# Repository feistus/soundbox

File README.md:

# Soundbox
This device plays soundfiles from a SD Card using the [https://github.com/TMRh20/TMRpcm](TMRpcm) lib.

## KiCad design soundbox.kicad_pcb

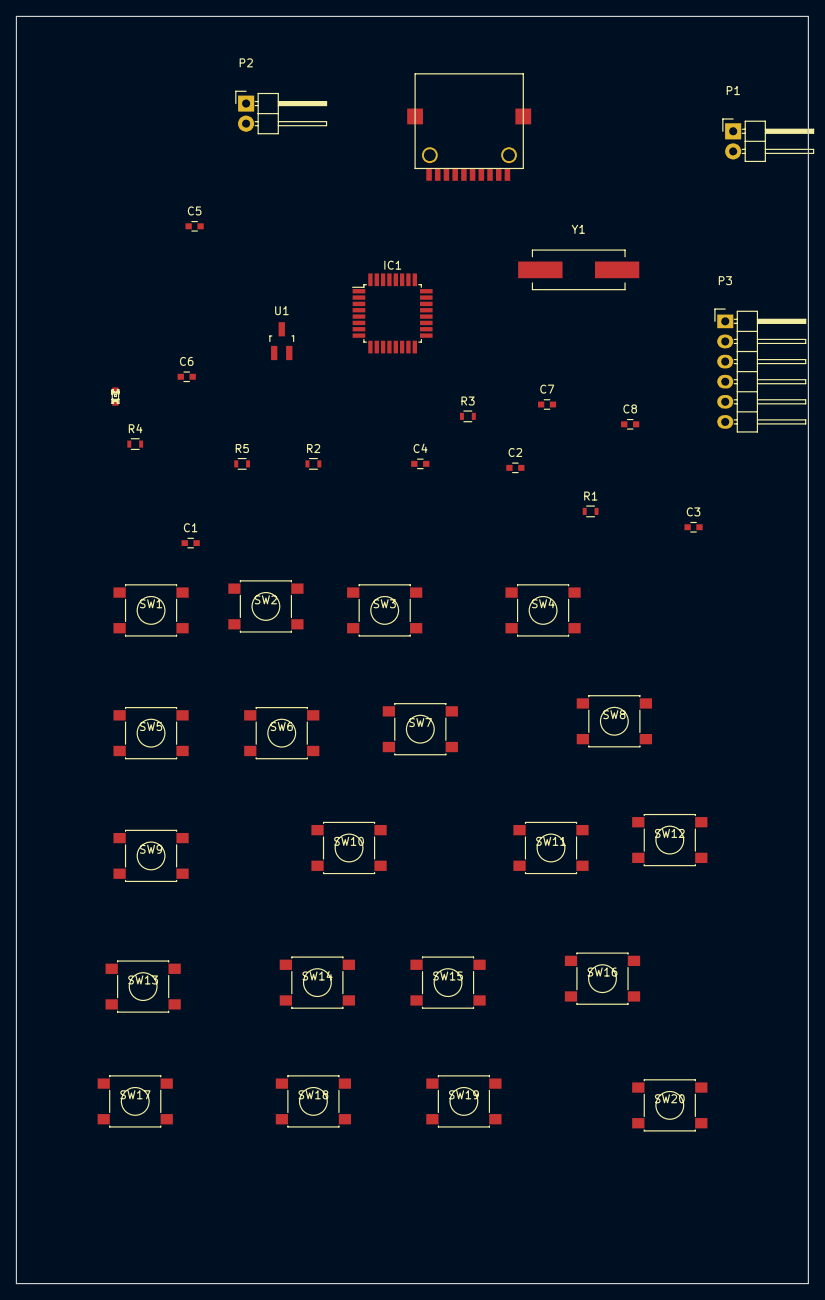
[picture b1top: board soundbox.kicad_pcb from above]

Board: 2 copper layers, 100.0 x 160.0 mm, 41 parts (0 on the bottom side), 27 nets, no tracks yet.

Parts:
C1, C2, C3, C4, C5, C8: 100n; C_0603
C6, C7: 23p; C_0603
D1: LED; led-CHIPLED_0603
IC1: ATMEGA328-A; TQFP-32_7x7mm_Pitch0.8mm
J1: µSD; MICRO_SD_CARD_HOLDER
P1, P2: CONN_01X02; Pin_Header_Angled_1x02
P3: CONN_01X06; Pin_Header_Angled_1x06
R1: 220R; R_0603
R2: 0R; R_0603
R3, R5: 1M; R_0603
R4: 15k; R_0603
SW1, SW2, SW3, SW4, SW5, SW6, SW7, SW8, SW9, SW10, SW11, SW12, SW13, SW14, SW15, SW16, SW17, SW18, SW19, SW20: SW_PUSH; SW_SPST_PTS645
U1: MCP1700; SOT-23_Handsoldering
Y1: 16MHz; Crystal_HC49-SD_SMD

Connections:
+3V3: C2.1, C8.2, IC1.4, IC1.6, IC1.18, IC1.20, J1.4, P3.3, U1.2
+12V: C1.1, P1.1, U1.3
/AF_OUT: C4.2, P2.1, R4.1, R5.2
/COL1: IC1.28, SW16.1, SW17.1, SW18.1, SW19.1, SW20.1
/COL2: SW11.1, SW12.1, SW13.1, SW14.1, SW15.1
/COL2/RXD: IC1.30, P3.5
/COL3: SW6.1, SW7.1, SW8.1, SW9.1, SW10.1
/COL3/TXD: IC1.31, P3.4
/COL4: IC1.32, SW1.1, SW2.1, SW3.1, SW4.1, SW5.1
/CS: IC1.2, J1.2
/DTR: C5.2, P3.6
/LED: IC1.1, R1.2
/MISO: IC1.16, J1.7
/MOSI: IC1.15, J1.3
/PWM_OUT: IC1.13, R2.2
/ROW1: IC1.23, SW1.2, SW6.2, SW11.2, SW16.2
/ROW2: IC1.24, SW2.2, SW7.2, SW12.2, SW17.2
/ROW3: IC1.25, SW3.2, SW8.2, SW13.2, SW18.2
/ROW4: IC1.26, SW4.2, SW9.2, SW14.2, SW19.2
/ROW5: IC1.27, SW5.2, SW10.2, SW15.2, SW20.2
/SCK: IC1.17, J1.5
/SD_SW: IC1.14, J1.9
/XTAL1: C6.2, IC1.7, Y1.2
/XTAL2: C7.2, IC1.8, Y1.1
/~RESET: C5.1, IC1.29
GND: C1.2, C2.2, C3.1, C4.1, C6.1, C7.1, C8.1, IC1.3, IC1.5, IC1.21, J1.6, J1.10, P1.2, P2.2, P3.1, R3.1, R5.1, U1.1
unnamed: C3.2, R2.1, R3.2, R4.2

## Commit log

2016-07-19 change Link in README
2016-07-21 final version of schematic packages assigned raw placement on layout
